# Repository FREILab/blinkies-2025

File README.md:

A PCB for freilab TdoW. 
Used svg2shenzen to import vectors to footprint.

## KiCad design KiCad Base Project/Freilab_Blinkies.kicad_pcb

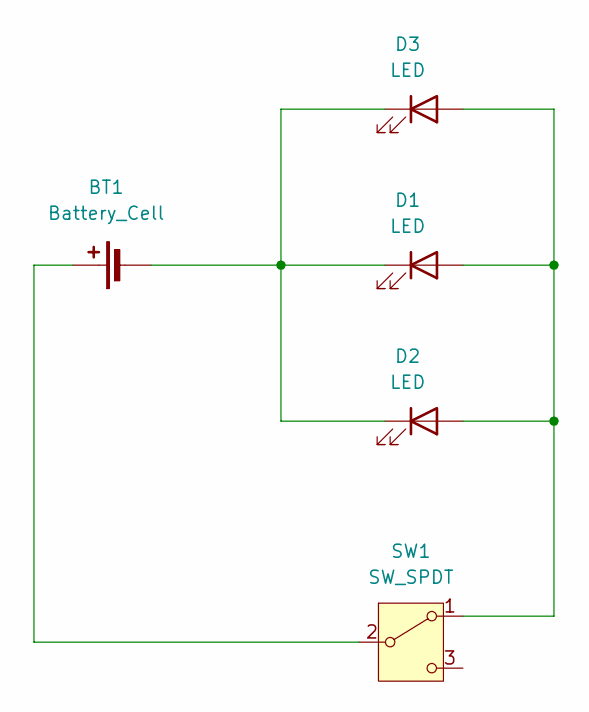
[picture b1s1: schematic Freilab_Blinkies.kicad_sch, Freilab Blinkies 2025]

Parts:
BT1: Battery_Cell; BatteryHolder_Keystone_1060_1x2032
D1, D2, D3: LED; BigPad_5mm LED
SW1: SW_SPDT; SW_Toggle_2P1T_5pin

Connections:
unnamed: BT1.1 (+), SW1.2 (B)
unnamed: BT1.2 (-), D1.1 (K), D2.1 (K), D3.1 (K)
unnamed: D1.2 (A), D2.2 (A), D3.2 (A), SW1.1 (A)

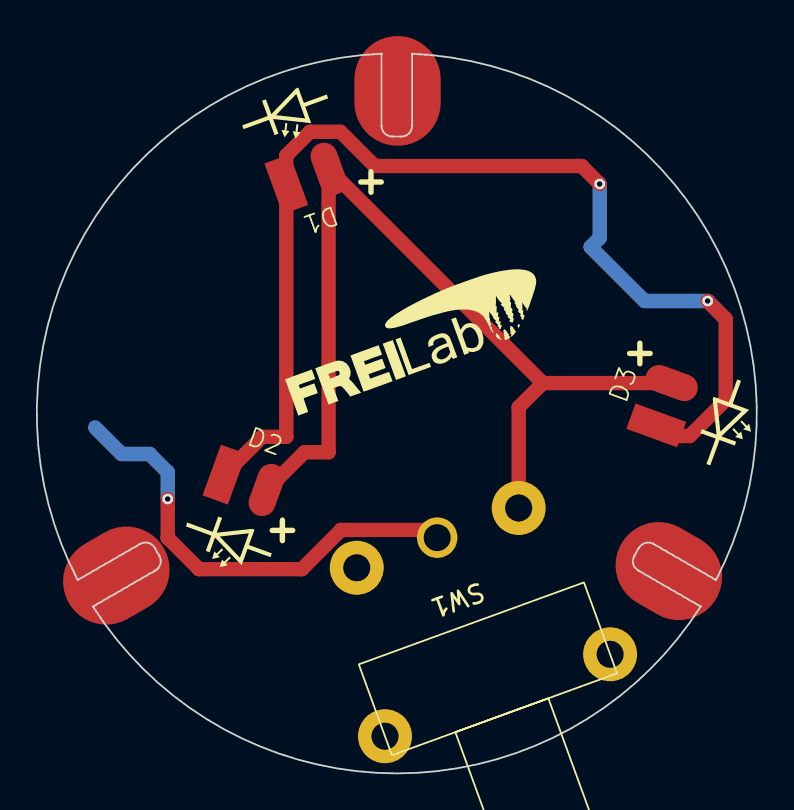
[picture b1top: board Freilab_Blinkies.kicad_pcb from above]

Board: 2 copper layers, 40.0 x 40.0 mm, 5 parts (1 on the bottom side), 3 nets.

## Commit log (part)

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2025-04-20 inital schematic
2025-04-21 added freilab logo svg
2025-04-21 added CR2032 holder datasheet
2025-04-28 Added CAD prototype for blinkie as well as DXF sketches
2025-05-06 updated Blinkie to 3-tabs
2025-05-06 Updated Base Sketch
2025-05-08 WIP svg
2025-05-08 Final Topper PCB Project & Source SVG
2025-05-08 Added gerbers for finan pcb topper
2025-05-09 Added Base Project, restarted PCB layout, added gerbers for base
2025-05-11 Fixed Base DRC Errors, added Tab project & gerbers
2025-05-11 Added final gerbers for the 3 subprojects
2025-05-11 WIP Tab project
2025-05-11 fix corners
2025-05-11 Removed B.Mask on Topper PCB
2025-05-11 Added Topper production files
2025-05-11 Removed old gerbers used plugin to generate
2025-06-17 Finale Fertigungsdatein
